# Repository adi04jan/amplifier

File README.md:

# Eagle Audio Amplifier 
It is a small audio amplifier for creating bass(low pass filter effect) on a given input signal

## Specifications

**Build** : v1.0

**IDE used** : [Autodesk Eagle](https://www.autodesk.com/products/eagle/overview)

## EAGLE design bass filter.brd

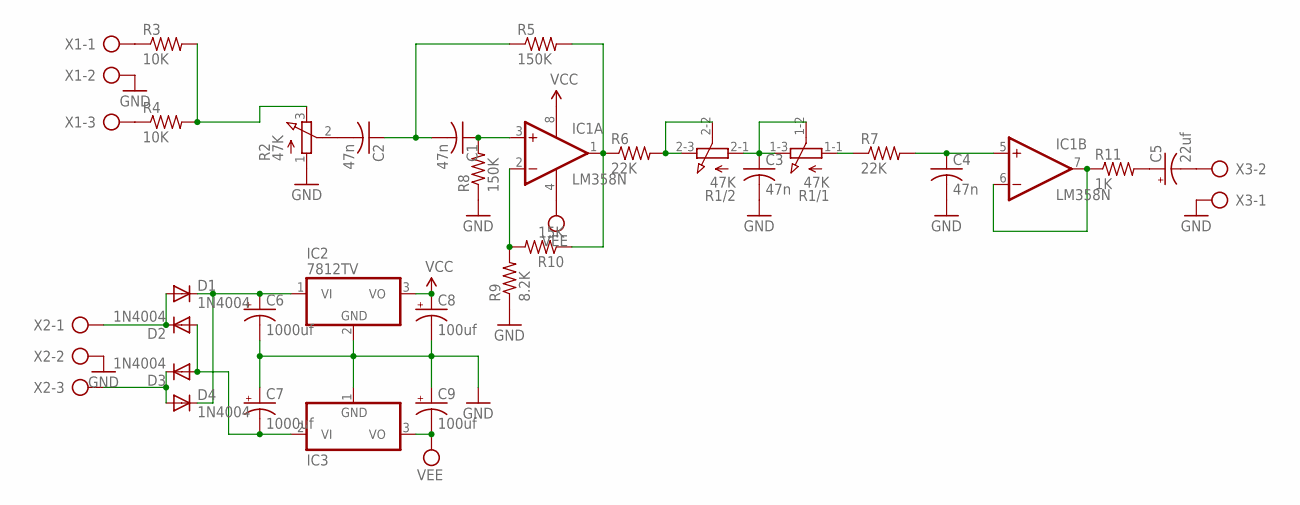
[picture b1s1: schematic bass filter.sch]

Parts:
C1, C2, C3, C4: 47n; C050-045X075
C5: 22uf; E2,5-6E
C6, C7: 1000uf; E5-13
C8, C9: 100uf; E2,5-6
D1, D2, D3, D4: 1N4004; DO41-10
IC1: LM358N; DIL08
IC2: 7812TV; TO220V
IC3: 7912T; TO220H
R1: 47K; 3RP/1610G
R2: 47K; 3RP/1610N
R3, R4: 10K; 0805-THM
R5, R8: 150K; 0805-THM
R6, R7: 22K; 0805-THM
R9: 8.2K; 0805-THM
R10: 15K; 0805-THM
R11: 1K; 0805-THM
X1, X2: AK300/3
X3: AK300/2

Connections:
GND: C3.2, C4.2, C6.-, C7.+, C8.-, C9.+, IC2.2 (GND), IC3.1 (GND), R2.1 (A), R8.1, R9.1, X1.2, X2.2, X3.1
unnamed: C1.1, IC1.3 (+IN), R8.2
unnamed: C1.2, C2.1, R5.1
unnamed: C2.2, R2.2 (S)
unnamed: IC1.1 (OUT), R5.2, R6.1, R10.1
unnamed: C4.1, IC1.5 (+IN), R7.2
unnamed: R1.2-2 (S), R1.2-3 (E), R6.2
unnamed: C3.1, R1.1-2 (S), R1.1-3 (E), R1.2-1 (A)
unnamed: R1.1-1 (A), R7.1
unnamed: IC1.2 (-IN), R9.2, R10.2
unnamed: R2.3 (E), R3.2, R4.2
unnamed: IC1.6 (-IN), IC1.7 (OUT), R11.1
unnamed: C5.+, R11.2
unnamed: R3.1, X1.1
unnamed: C5.-, X3.2
unnamed: R4.1, X1.3
unnamed: D1.A, D2.C, X2.1
unnamed: D3.C, D4.A, X2.3
unnamed: C7.-, D2.A, D3.A, IC3.2 (VI)
unnamed: C6.+, D1.C, D4.C, IC2.1 (VI)
VCC: C8.+, IC1.8 (V+), IC2.3 (VO)
VEE: C9.-, IC1.4 (V-), IC3.3 (VO)

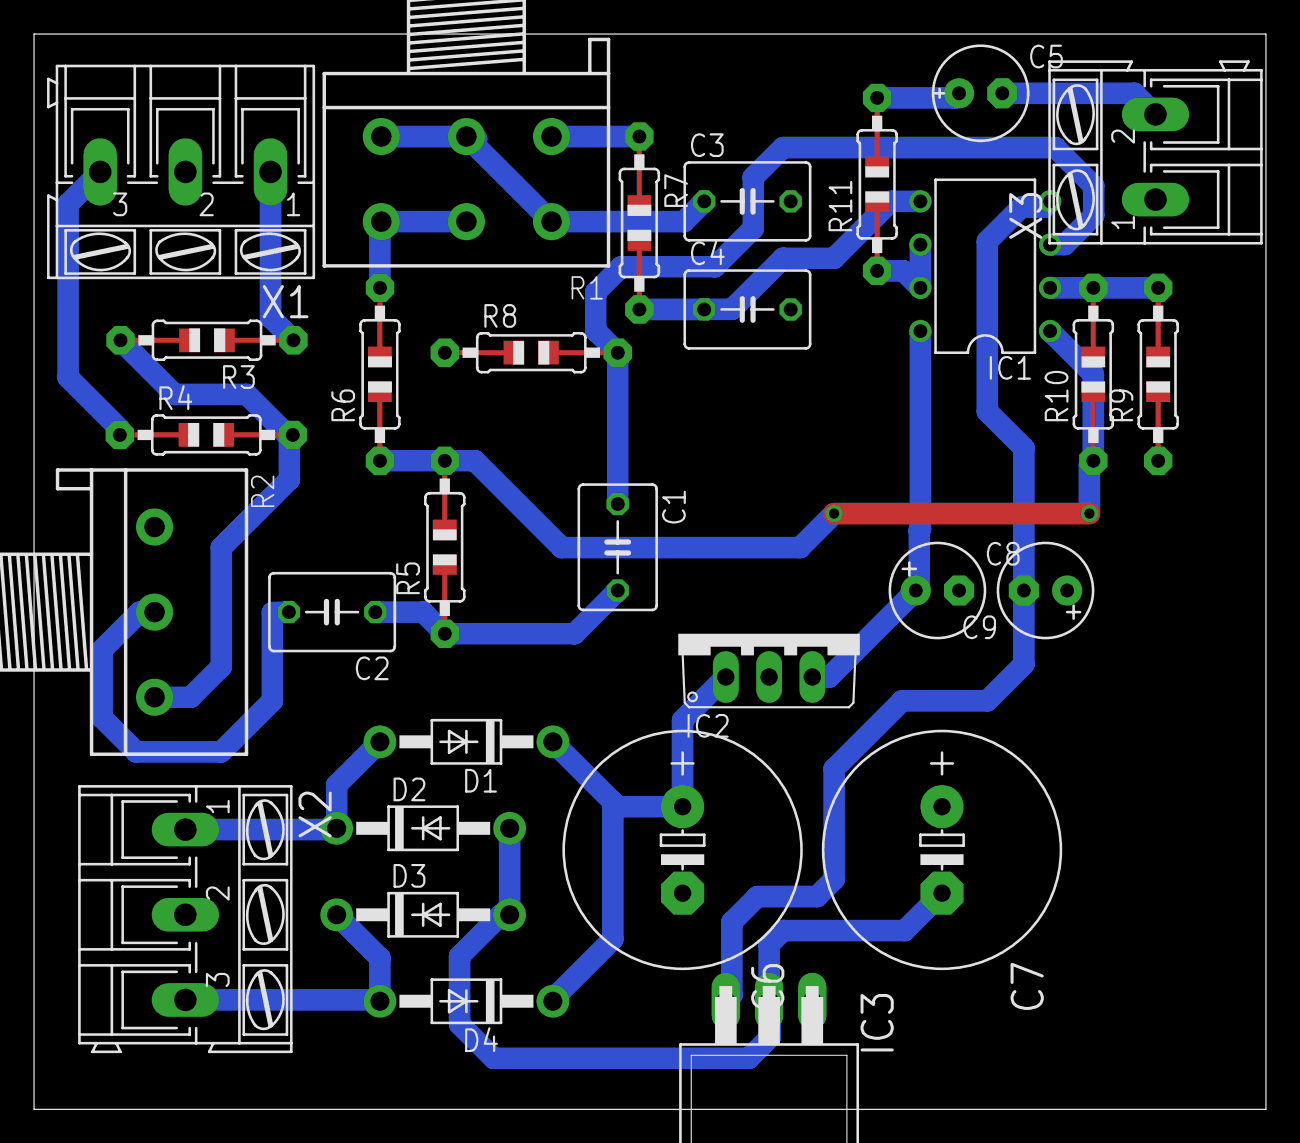
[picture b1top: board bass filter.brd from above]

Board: 2 copper layers, 72.4 x 63.2 mm, 30 parts (0 on the bottom side), 22 nets.

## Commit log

2017-02-05 Low Pass filter for Music System
    This circuit allow to pass only low frequency.
    Circuit use lm358 at core and can be replaced by any other op-amp
    It can be used as a pre-amp for Power amplifier.
    input voltage = +-12v DC
    gain is adjustable
    2 knob for volume and setting cutoff frequency

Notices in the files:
parts and their libraries:
SparkFun-Aesthetics: Licensing: Creative Commons ShareAlike 4.0 International - https://creativecommons.org/licenses/by-sa/4.0
